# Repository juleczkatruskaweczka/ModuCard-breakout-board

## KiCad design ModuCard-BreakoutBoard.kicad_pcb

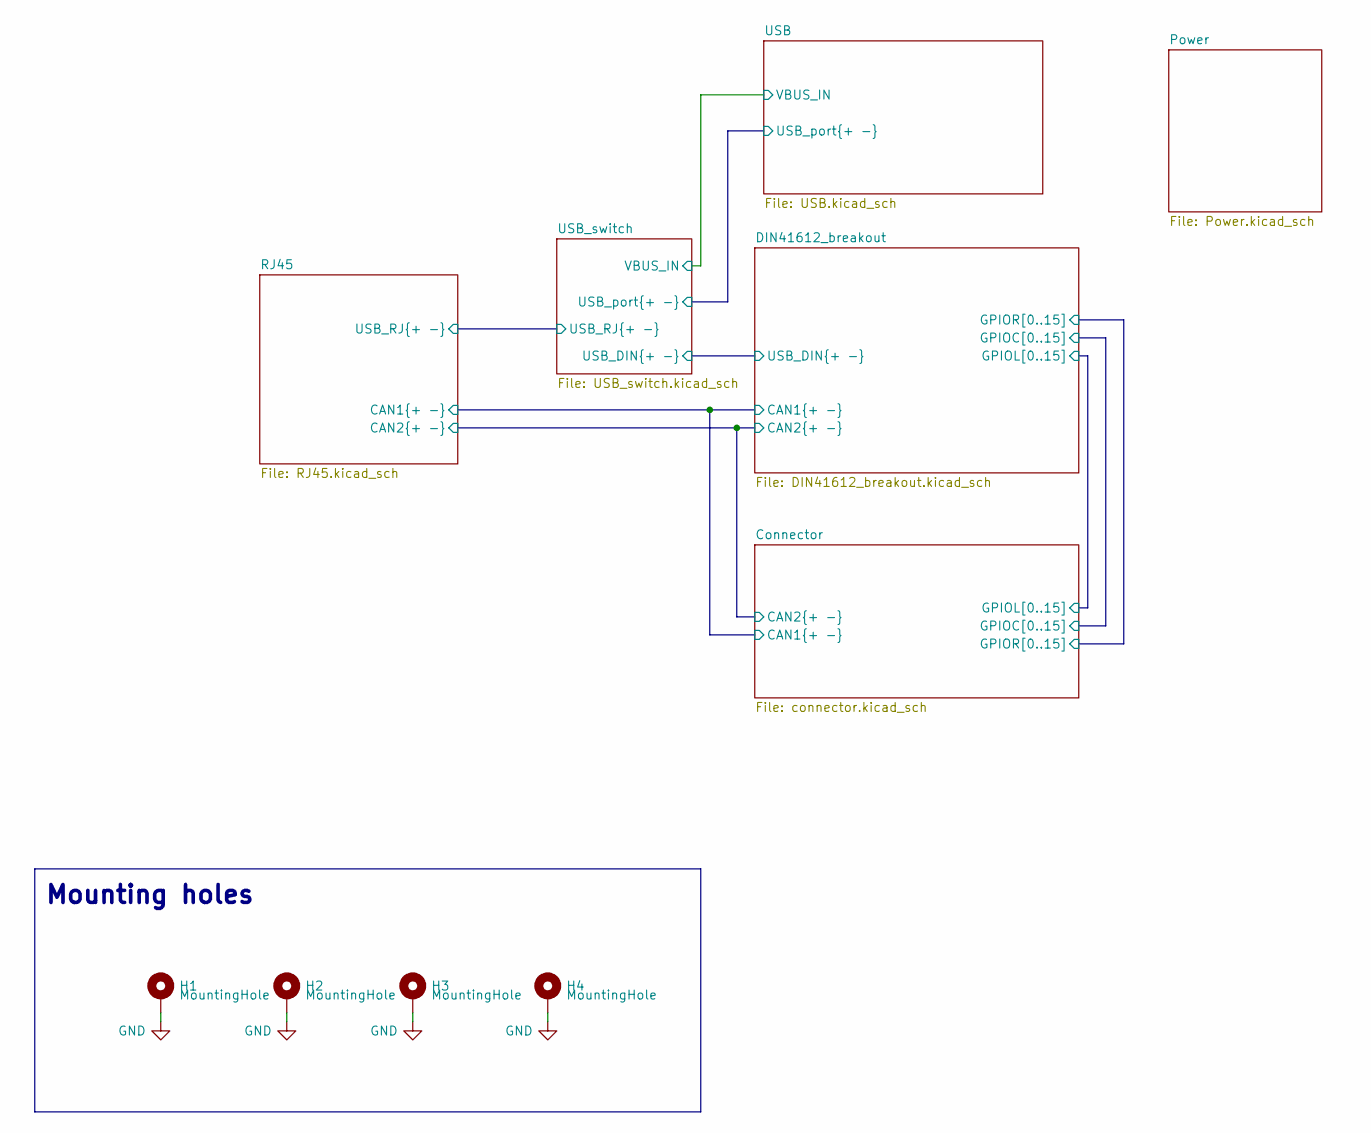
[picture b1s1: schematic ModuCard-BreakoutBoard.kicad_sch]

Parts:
H1, H2, H3, H4: MountingHole; MountingHole_2.7mm_M2.5_DIN965_Pad

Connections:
GND: H1.1, H2.1, H3.1, H4.1; also elsewhere on the board

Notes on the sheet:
Mounting holes

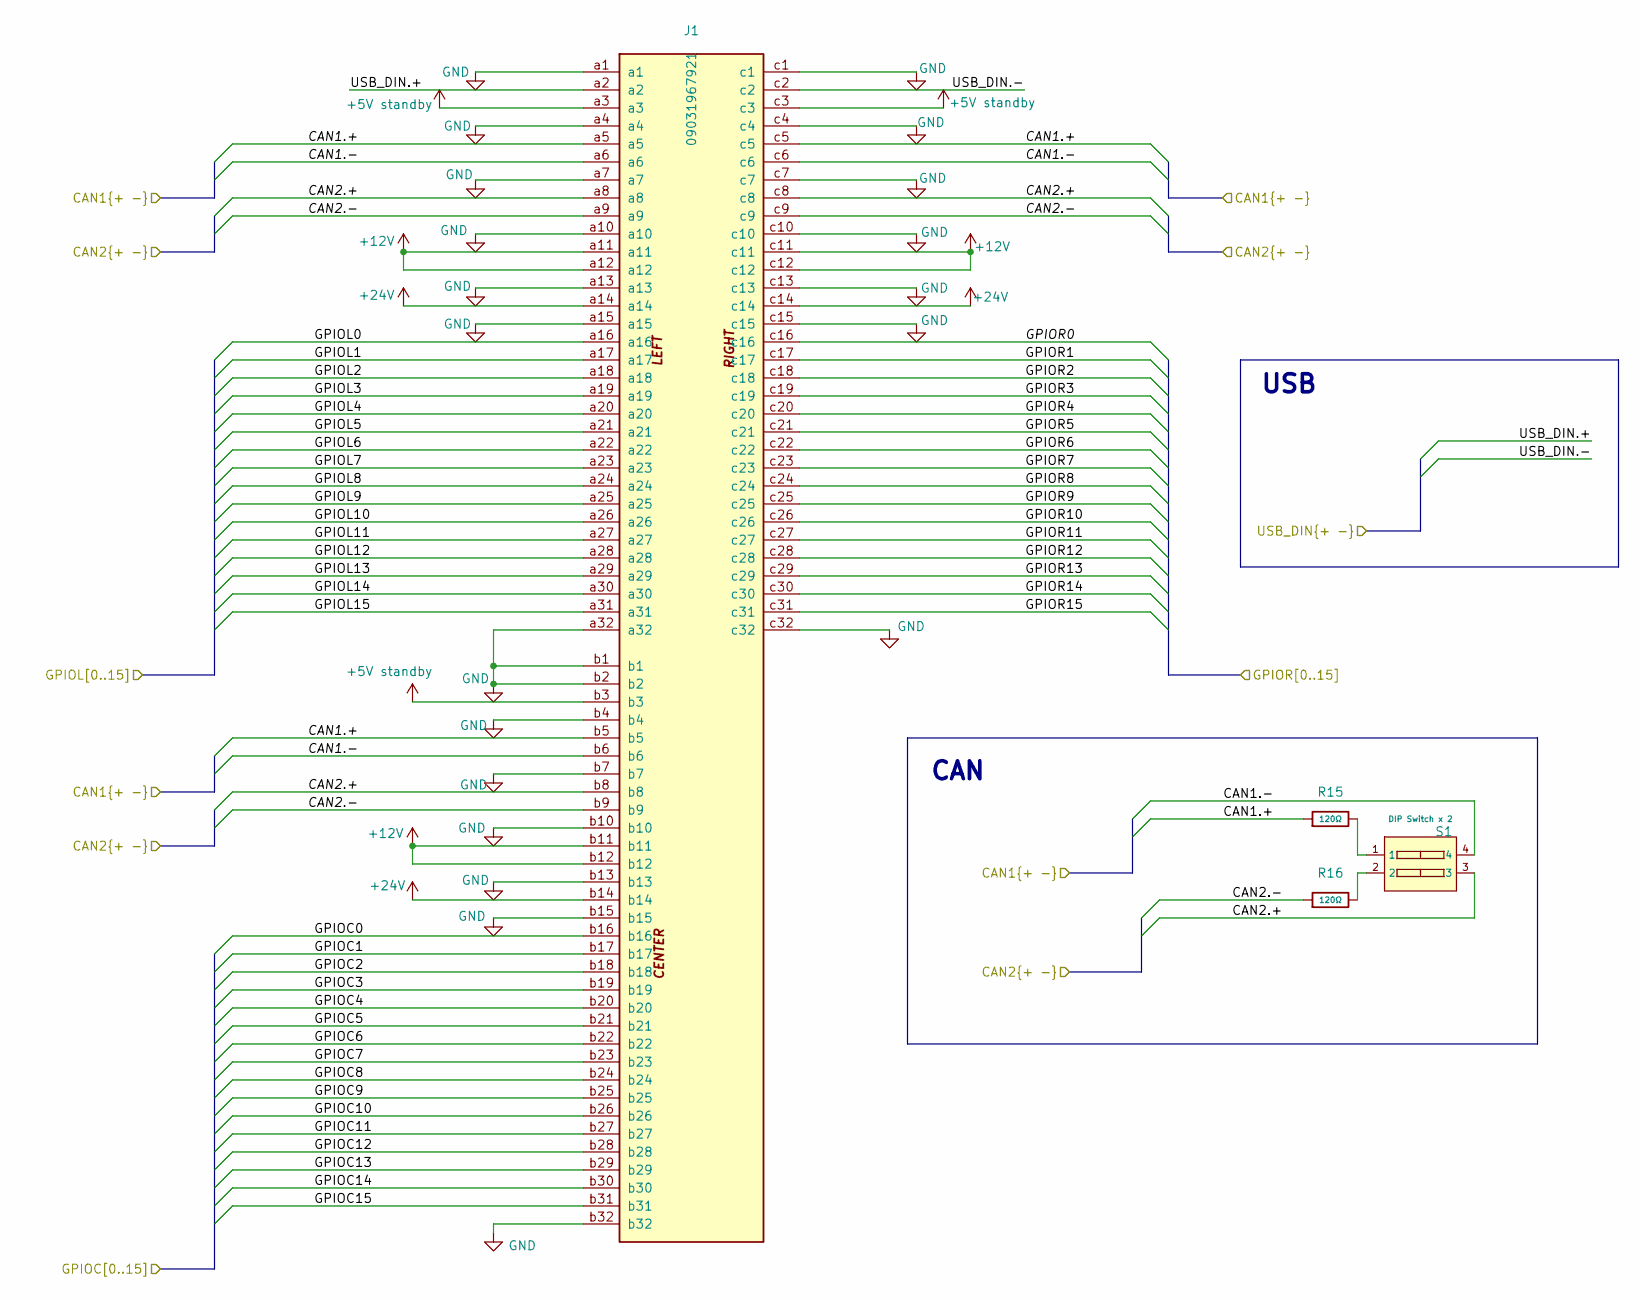
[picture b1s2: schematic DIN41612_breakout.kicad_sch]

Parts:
J1: 09031967921; DIN41612_R_3x32_Male_Vertical_THT; PARTREV D
R15, R16: 120Ω; R_0603; Overload Voltage (Max) 75V; Tolerance ±1%; Part 0603WAF1200T5E; LCSC C22787
S1: DIP Switch x 2; SW_DIP_SPSTx02_Slide_9.78x7.26mm_W7.62mm_P2.54mm; Current Rating 25mA; Voltage Rating 24V; Part 218-2LPSTR; LCSC C2961921

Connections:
+5V standby: J1.a3, J1.b3, J1.c3; also elsewhere on the board
+12V: J1.a11, J1.a12, J1.b11, J1.b12, J1.c11, J1.c12; also elsewhere on the board
+24V: J1.a14, J1.b14, J1.c14; also elsewhere on the board
/Connector/CAN1.+: J1.a5, J1.b5, J1.c5, R15.1; also elsewhere on the board
/Connector/CAN1.-: J1.a6, J1.b6, J1.c6, S1.4; also elsewhere on the board
/Connector/CAN2.+: J1.a8, J1.b8, J1.c8, S1.3; also elsewhere on the board
/Connector/CAN2.-: J1.a9, J1.b9, J1.c9, R16.1; also elsewhere on the board
/Connector/GPIOC0: J1.b16; also elsewhere on the board
/Connector/GPIOC1: J1.b17; also elsewhere on the board
/Connector/GPIOC2: J1.b18; also elsewhere on the board
/Connector/GPIOC3: J1.b19; also elsewhere on the board
/Connector/GPIOC4: J1.b20; also elsewhere on the board
/Connector/GPIOC5: J1.b21; also elsewhere on the board
/Connector/GPIOC6: J1.b22; also elsewhere on the board
/Connector/GPIOC7: J1.b23; also elsewhere on the board
/Connector/GPIOC8: J1.b24; also elsewhere on the board
/Connector/GPIOC9: J1.b25; also elsewhere on the board
/Connector/GPIOC10: J1.b26; also elsewhere on the board
/Connector/GPIOC11: J1.b27; also elsewhere on the board
/Connector/GPIOC12: J1.b28; also elsewhere on the board
/Connector/GPIOC13: J1.b29; also elsewhere on the board
/Connector/GPIOC14: J1.b30; also elsewhere on the board
/Connector/GPIOC15: J1.b31; also elsewhere on the board
/Connector/GPIOL0: J1.a16; also elsewhere on the board
/Connector/GPIOL1: J1.a17; also elsewhere on the board
/Connector/GPIOL2: J1.a18; also elsewhere on the board
/Connector/GPIOL3: J1.a19; also elsewhere on the board
/Connector/GPIOL4: J1.a20; also elsewhere on the board
/Connector/GPIOL5: J1.a21; also elsewhere on the board
/Connector/GPIOL6: J1.a22; also elsewhere on the board
/Connector/GPIOL7: J1.a23; also elsewhere on the board
/Connector/GPIOL8: J1.a24; also elsewhere on the board
/Connector/GPIOL9: J1.a25; also elsewhere on the board
/Connector/GPIOL10: J1.a26; also elsewhere on the board
/Connector/GPIOL11: J1.a27; also elsewhere on the board
/Connector/GPIOL12: J1.a28; also elsewhere on the board
/Connector/GPIOL13: J1.a29; also elsewhere on the board
/Connector/GPIOL14: J1.a30; also elsewhere on the board
/Connector/GPIOL15: J1.a31; also elsewhere on the board
/Connector/GPIOR0: J1.c16; also elsewhere on the board
/Connector/GPIOR1: J1.c17; also elsewhere on the board
/Connector/GPIOR2: J1.c18; also elsewhere on the board
/Connector/GPIOR3: J1.c19; also elsewhere on the board
/Connector/GPIOR4: J1.c20; also elsewhere on the board
/Connector/GPIOR5: J1.c21; also elsewhere on the board
/Connector/GPIOR6: J1.c22; also elsewhere on the board
/Connector/GPIOR7: J1.c23; also elsewhere on the board
/Connector/GPIOR8: J1.c24; also elsewhere on the board
/Connector/GPIOR9: J1.c25; also elsewhere on the board
/Connector/GPIOR10: J1.c26; also elsewhere on the board
/Connector/GPIOR11: J1.c27; also elsewhere on the board
/Connector/GPIOR12: J1.c28; also elsewhere on the board
/Connector/GPIOR13: J1.c29; also elsewhere on the board
/Connector/GPIOR14: J1.c30; also elsewhere on the board
/Connector/GPIOR15: J1.c31; also elsewhere on the board
/DIN41612_breakout/USB_DIN.+: J1.a2; also elsewhere on the board
/DIN41612_breakout/USB_DIN.-: J1.c2; also elsewhere on the board
GND: J1.a1, J1.a4, J1.a7, J1.a10, J1.a13, J1.a15, J1.a32, J1.b1, J1.b2, J1.b4, J1.b7, J1.b10, J1.b13, J1.b15, J1.b32, J1.c1, J1.c4, J1.c7, J1.c10, J1.c13, J1.c15, J1.c32; also elsewhere on the board
unnamed: R15.2, S1.1
unnamed: R16.2, S1.2

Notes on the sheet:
CAN
USB

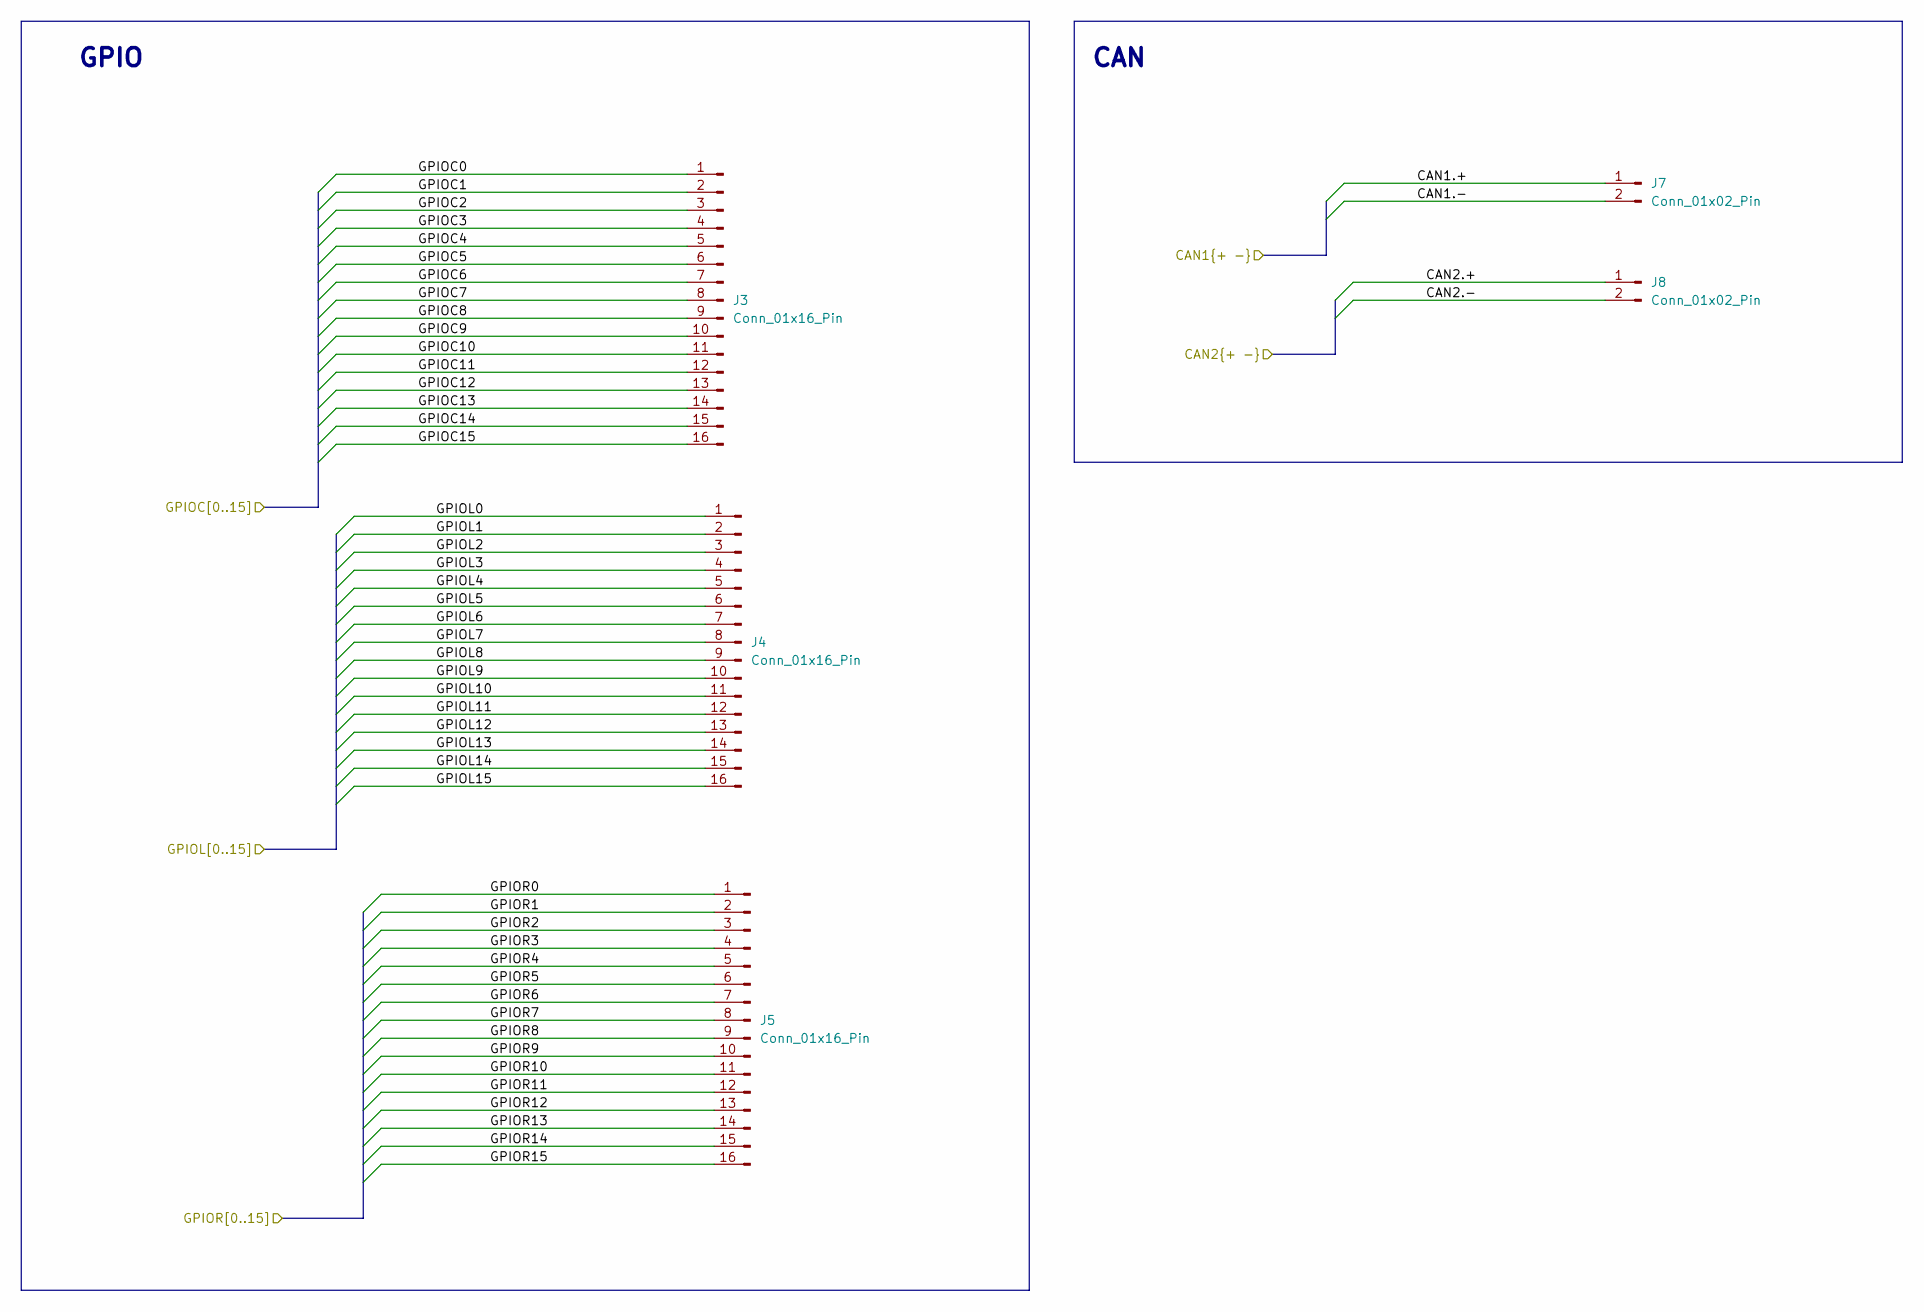
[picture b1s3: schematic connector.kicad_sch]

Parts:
J3, J4, J5: Conn_01x16_Pin; PinHeader_1x16_P2.54mm_Vertical
J7, J8: Conn_01x02_Pin; PinHeader_1x02_P2.54mm_Vertical

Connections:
/Connector/CAN1.+: J7.1; also elsewhere on the board
/Connector/CAN1.-: J7.2; also elsewhere on the board
/Connector/CAN2.+: J8.1; also elsewhere on the board
/Connector/CAN2.-: J8.2; also elsewhere on the board
/Connector/GPIOC0: J3.1; also elsewhere on the board
/Connector/GPIOC1: J3.2; also elsewhere on the board
/Connector/GPIOC2: J3.3; also elsewhere on the board
/Connector/GPIOC3: J3.4; also elsewhere on the board
/Connector/GPIOC4: J3.5; also elsewhere on the board
/Connector/GPIOC5: J3.6; also elsewhere on the board
/Connector/GPIOC6: J3.7; also elsewhere on the board
/Connector/GPIOC7: J3.8; also elsewhere on the board
/Connector/GPIOC8: J3.9; also elsewhere on the board
/Connector/GPIOC9: J3.10; also elsewhere on the board
/Connector/GPIOC10: J3.11; also elsewhere on the board
/Connector/GPIOC11: J3.12; also elsewhere on the board
/Connector/GPIOC12: J3.13; also elsewhere on the board
/Connector/GPIOC13: J3.14; also elsewhere on the board
/Connector/GPIOC14: J3.15; also elsewhere on the board
/Connector/GPIOC15: J3.16; also elsewhere on the board
/Connector/GPIOL0: J4.1; also elsewhere on the board
/Connector/GPIOL1: J4.2; also elsewhere on the board
/Connector/GPIOL2: J4.3; also elsewhere on the board
/Connector/GPIOL3: J4.4; also elsewhere on the board
/Connector/GPIOL4: J4.5; also elsewhere on the board
/Connector/GPIOL5: J4.6; also elsewhere on the board
/Connector/GPIOL6: J4.7; also elsewhere on the board
/Connector/GPIOL7: J4.8; also elsewhere on the board
/Connector/GPIOL8: J4.9; also elsewhere on the board
/Connector/GPIOL9: J4.10; also elsewhere on the board
/Connector/GPIOL10: J4.11; also elsewhere on the board
/Connector/GPIOL11: J4.12; also elsewhere on the board
/Connector/GPIOL12: J4.13; also elsewhere on the board
/Connector/GPIOL13: J4.14; also elsewhere on the board
/Connector/GPIOL14: J4.15; also elsewhere on the board
/Connector/GPIOL15: J4.16; also elsewhere on the board
/Connector/GPIOR0: J5.1; also elsewhere on the board
/Connector/GPIOR1: J5.2; also elsewhere on the board
/Connector/GPIOR2: J5.3; also elsewhere on the board
/Connector/GPIOR3: J5.4; also elsewhere on the board
/Connector/GPIOR4: J5.5; also elsewhere on the board
/Connector/GPIOR5: J5.6; also elsewhere on the board
/Connector/GPIOR6: J5.7; also elsewhere on the board
/Connector/GPIOR7: J5.8; also elsewhere on the board
/Connector/GPIOR8: J5.9; also elsewhere on the board
/Connector/GPIOR9: J5.10; also elsewhere on the board
/Connector/GPIOR10: J5.11; also elsewhere on the board
/Connector/GPIOR11: J5.12; also elsewhere on the board
/Connector/GPIOR12: J5.13; also elsewhere on the board
/Connector/GPIOR13: J5.14; also elsewhere on the board
/Connector/GPIOR14: J5.15; also elsewhere on the board
/Connector/GPIOR15: J5.16; also elsewhere on the board

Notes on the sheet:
CAN
GPIO

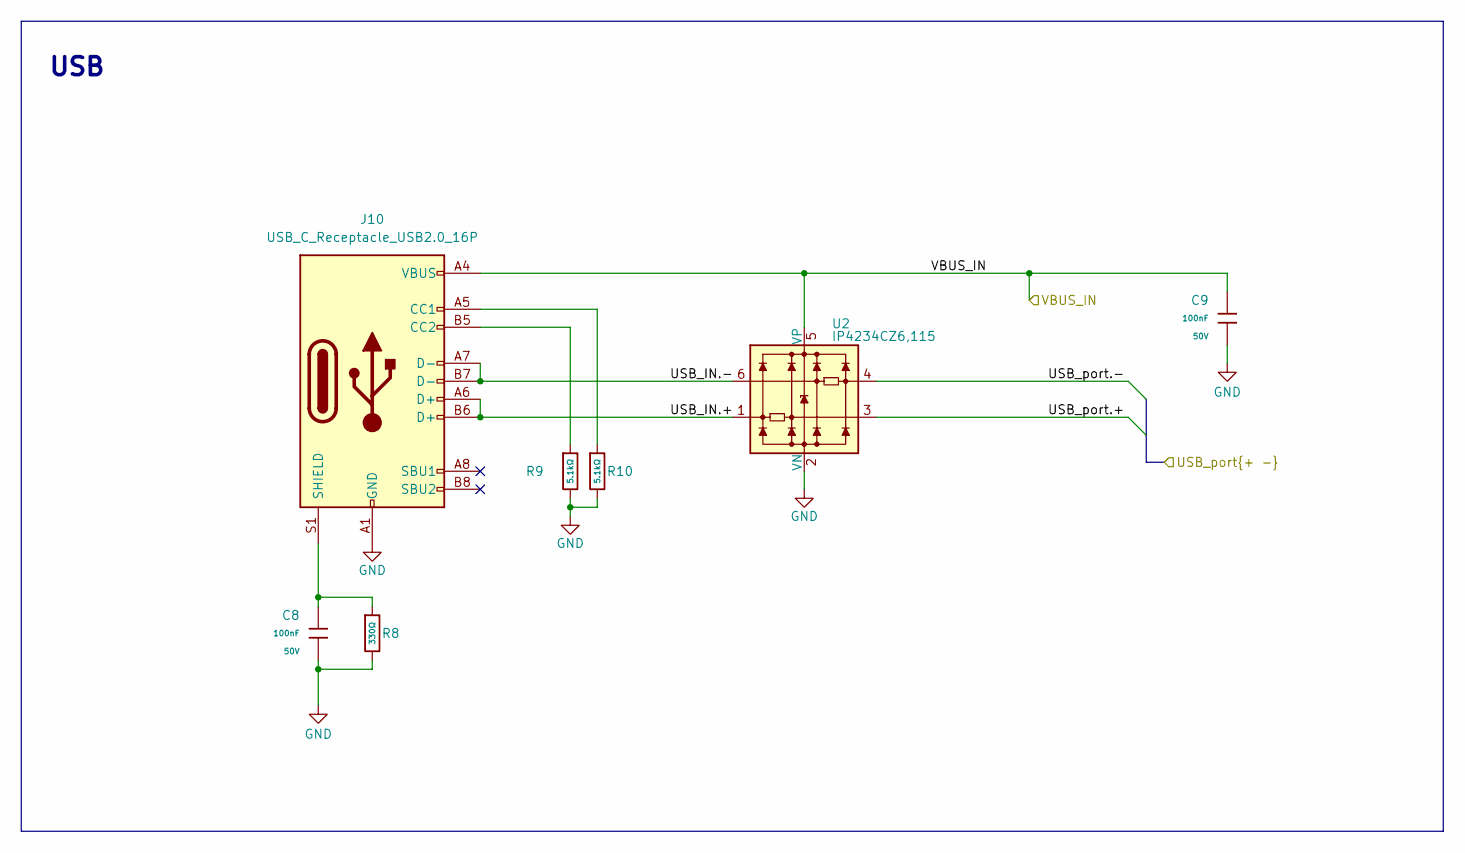
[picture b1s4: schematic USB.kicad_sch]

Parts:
C8, C9: 100nF; C_0402; Voltage Rated 50V; Tolerance ±10%; Part CL05B104KB54PNC; LCSC C307331
J10: USB_C_Receptacle_USB2.0_16P; USB_C_Receptacle_GCT_USB4105-xx-A_16P_TopMnt_Horizontal
R8: 330Ω; R_0402; Overload Voltage (Max) 50V; Tolerance ±1%; Part 0402WGF3300TCE; LCSC C25104
R9, R10: 5.1kΩ; R_0402; Overload Voltage (Max) 50V; Tolerance ±1%; Part 0402WGF5101TCE; LCSC C25905
U2: IP4234CZ6,115; SC-74-6_1.55x2.9mm_P0.95mm

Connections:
/USB/USB_IN.+: J10.A6 (D+), J10.B6 (D+), U2.1
/USB/USB_IN.-: J10.A7 (D-), J10.B7 (D-), U2.6
/USB/USB_port.+: U2.3; also elsewhere on the board
/USB/USB_port.-: U2.4; also elsewhere on the board
/USB/VBUS_IN: C9.1, J10.A4 (VBUS), J10.A9 (VBUS), J10.B4 (VBUS), J10.B9 (VBUS), U2.5 (VP); also elsewhere on the board
GND: C8.2, C9.2, J10.A1 (GND), J10.A12 (GND), J10.B1 (GND), J10.B12 (GND), R8.2, R9.2, R10.2, U2.2 (VN); also elsewhere on the board
unnamed: J10.A5 (CC1), R10.1
unnamed: J10.B5 (CC2), R9.1
unnamed: C8.1, J10.S1 (SHIELD), R8.1

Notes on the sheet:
USB

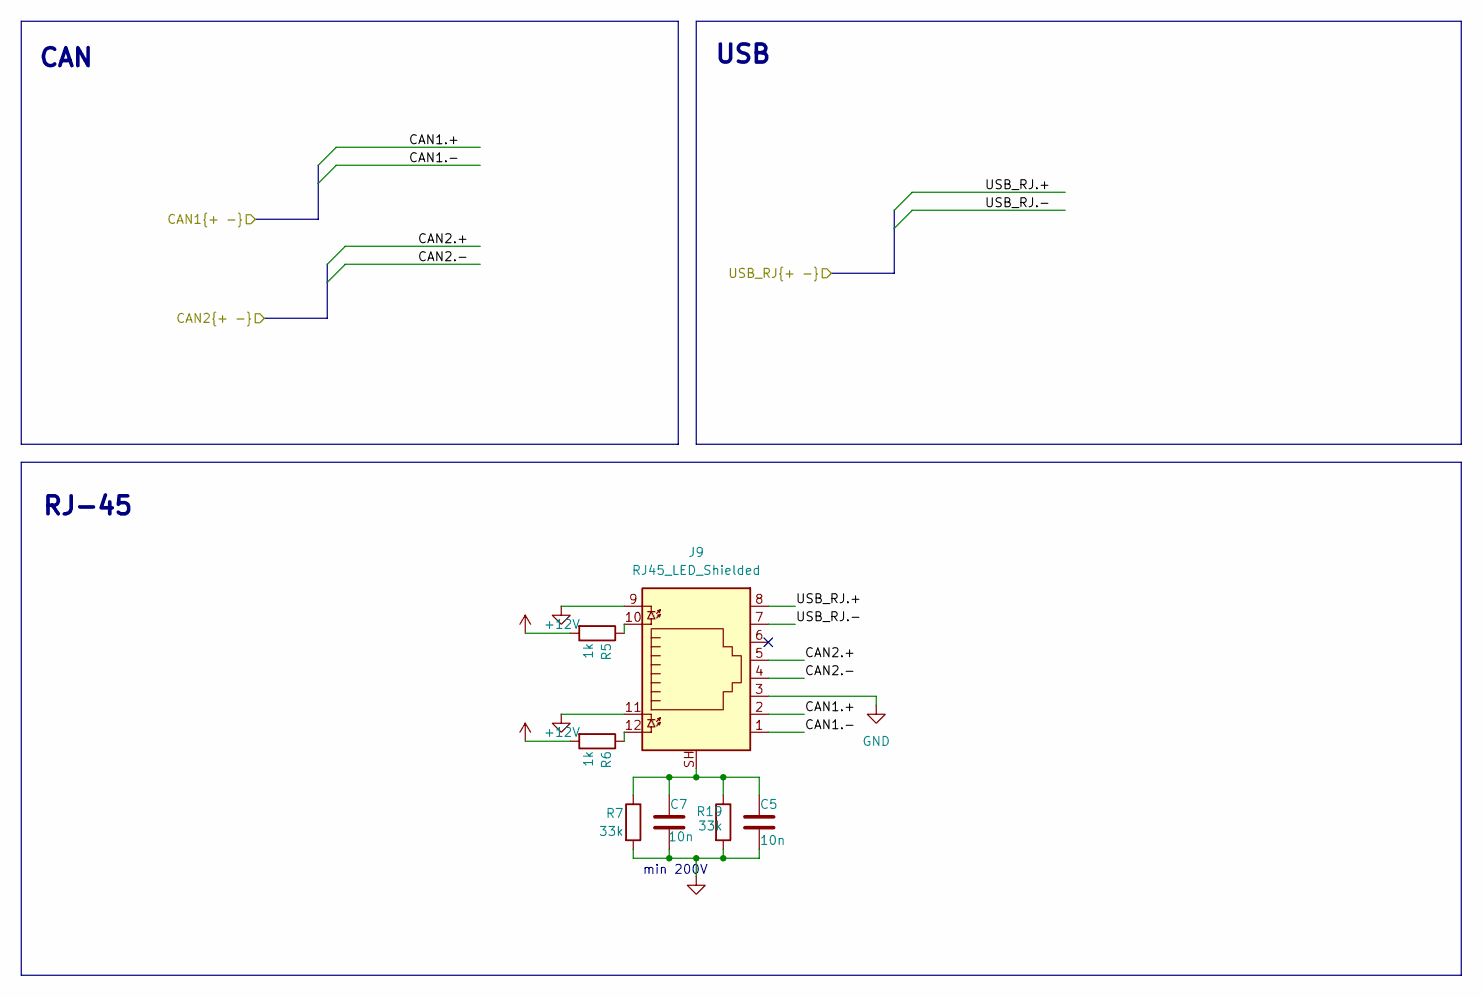
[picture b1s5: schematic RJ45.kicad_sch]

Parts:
C5, C7: 10n; C_0402_1005Metric
J9: RJ45_LED_Shielded; RJ45_Amphenol_RJHSE538X
R5, R6: 1k; R_0402_1005Metric
R7, R19: 33k; R_0402_1005Metric

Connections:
+12V: R5.2, R6.2; also elsewhere on the board
/Connector/CAN1.+: J9.2; also elsewhere on the board
/Connector/CAN1.-: J9.1; also elsewhere on the board
/Connector/CAN2.+: J9.5; also elsewhere on the board
/Connector/CAN2.-: J9.4; also elsewhere on the board
/RJ45/USB_RJ.+: J9.8; also elsewhere on the board
/RJ45/USB_RJ.-: J9.7; also elsewhere on the board
GND: C5.2, C7.2, J9.3, J9.9, J9.11, R7.2, R19.2; also elsewhere on the board
unnamed: C5.1, C7.1, J9.SH, R7.1, R19.1
unnamed: J9.10, R5.1
unnamed: J9.12, R6.1

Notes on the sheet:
USB
RJ-45
min 200V
CAN

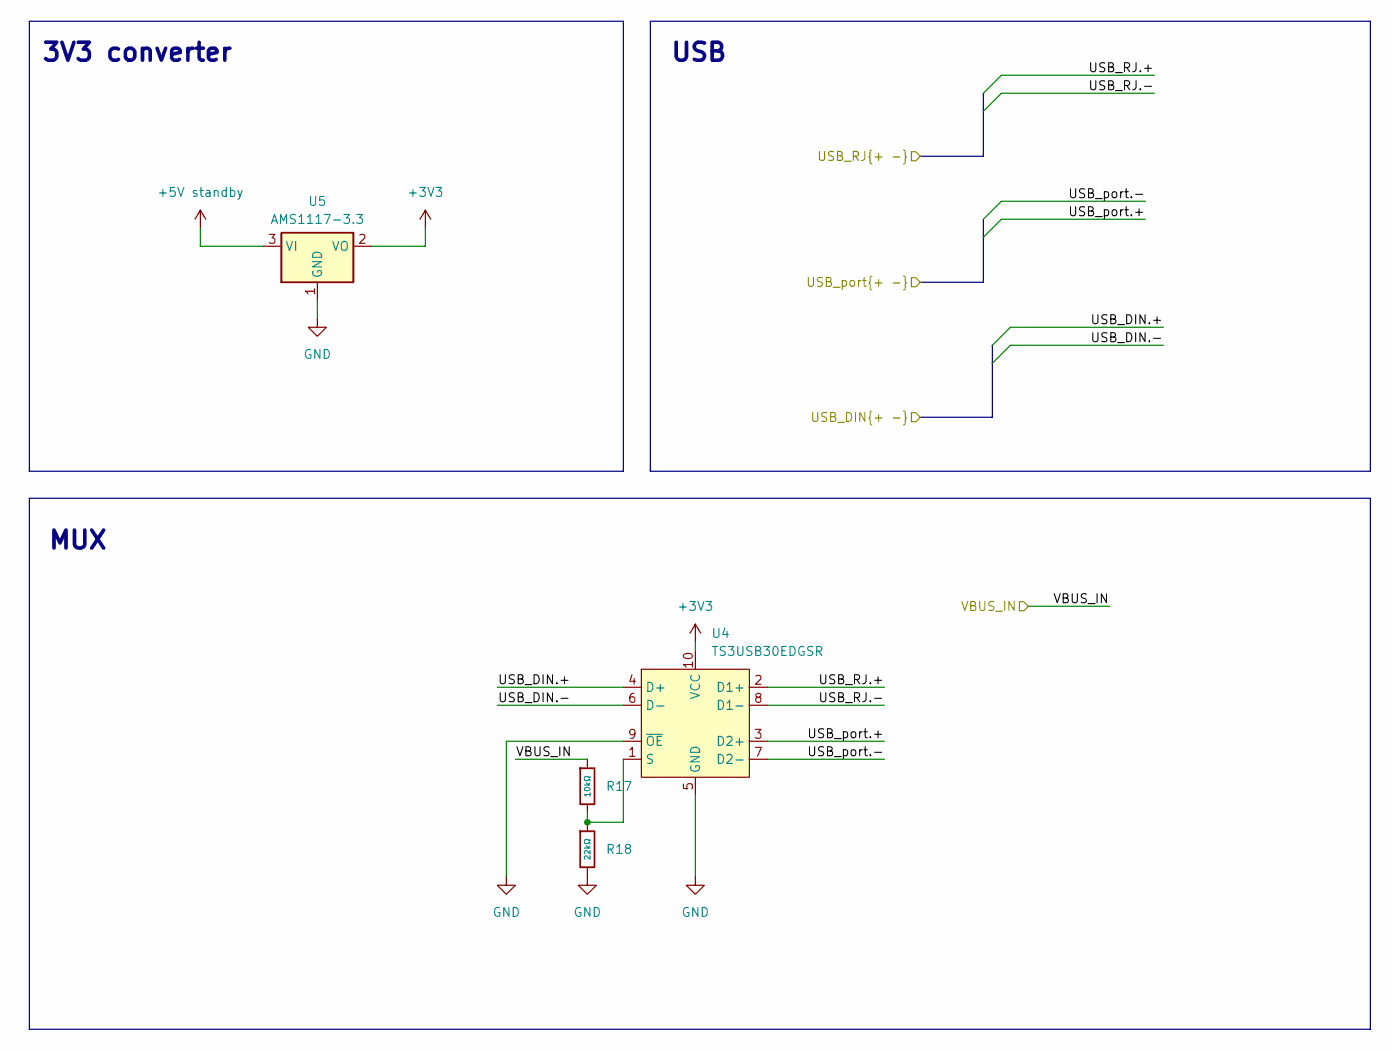
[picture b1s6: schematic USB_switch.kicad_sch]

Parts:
R17: 10kΩ; R_0603; Overload Voltage (Max) 75V; Tolerance ±1%; Part 0603WAF1002T5E; LCSC C25804
R18: 22kΩ; R_0402; Overload Voltage (Max) 50V; Tolerance ±1%; Part 0402WGF2202TCE; LCSC C25768
U4: TS3USB30EDGSR; VSSOP-10_3x3mm_P0.5mm
U5: AMS1117-3.3; SOT-223-3_TabPin2

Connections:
+3V3: U4.10 (VCC), U5.2 (VO)
+5V standby: U5.3 (VI); also elsewhere on the board
/DIN41612_breakout/USB_DIN.+: U4.4 (D+); also elsewhere on the board
/DIN41612_breakout/USB_DIN.-: U4.6 (D-); also elsewhere on the board
/RJ45/USB_RJ.+: U4.2 (D1+); also elsewhere on the board
/RJ45/USB_RJ.-: U4.8 (D1-); also elsewhere on the board
/USB/USB_port.+: U4.3 (D2+); also elsewhere on the board
/USB/USB_port.-: U4.7 (D2-); also elsewhere on the board
/USB/VBUS_IN: R17.1; also elsewhere on the board
GND: R18.2, U4.5 (GND), U4.9 (~OE), U5.1 (GND); also elsewhere on the board
unnamed: R17.2, R18.1, U4.1 (S)

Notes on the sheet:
USB
MUX
3V3 converter

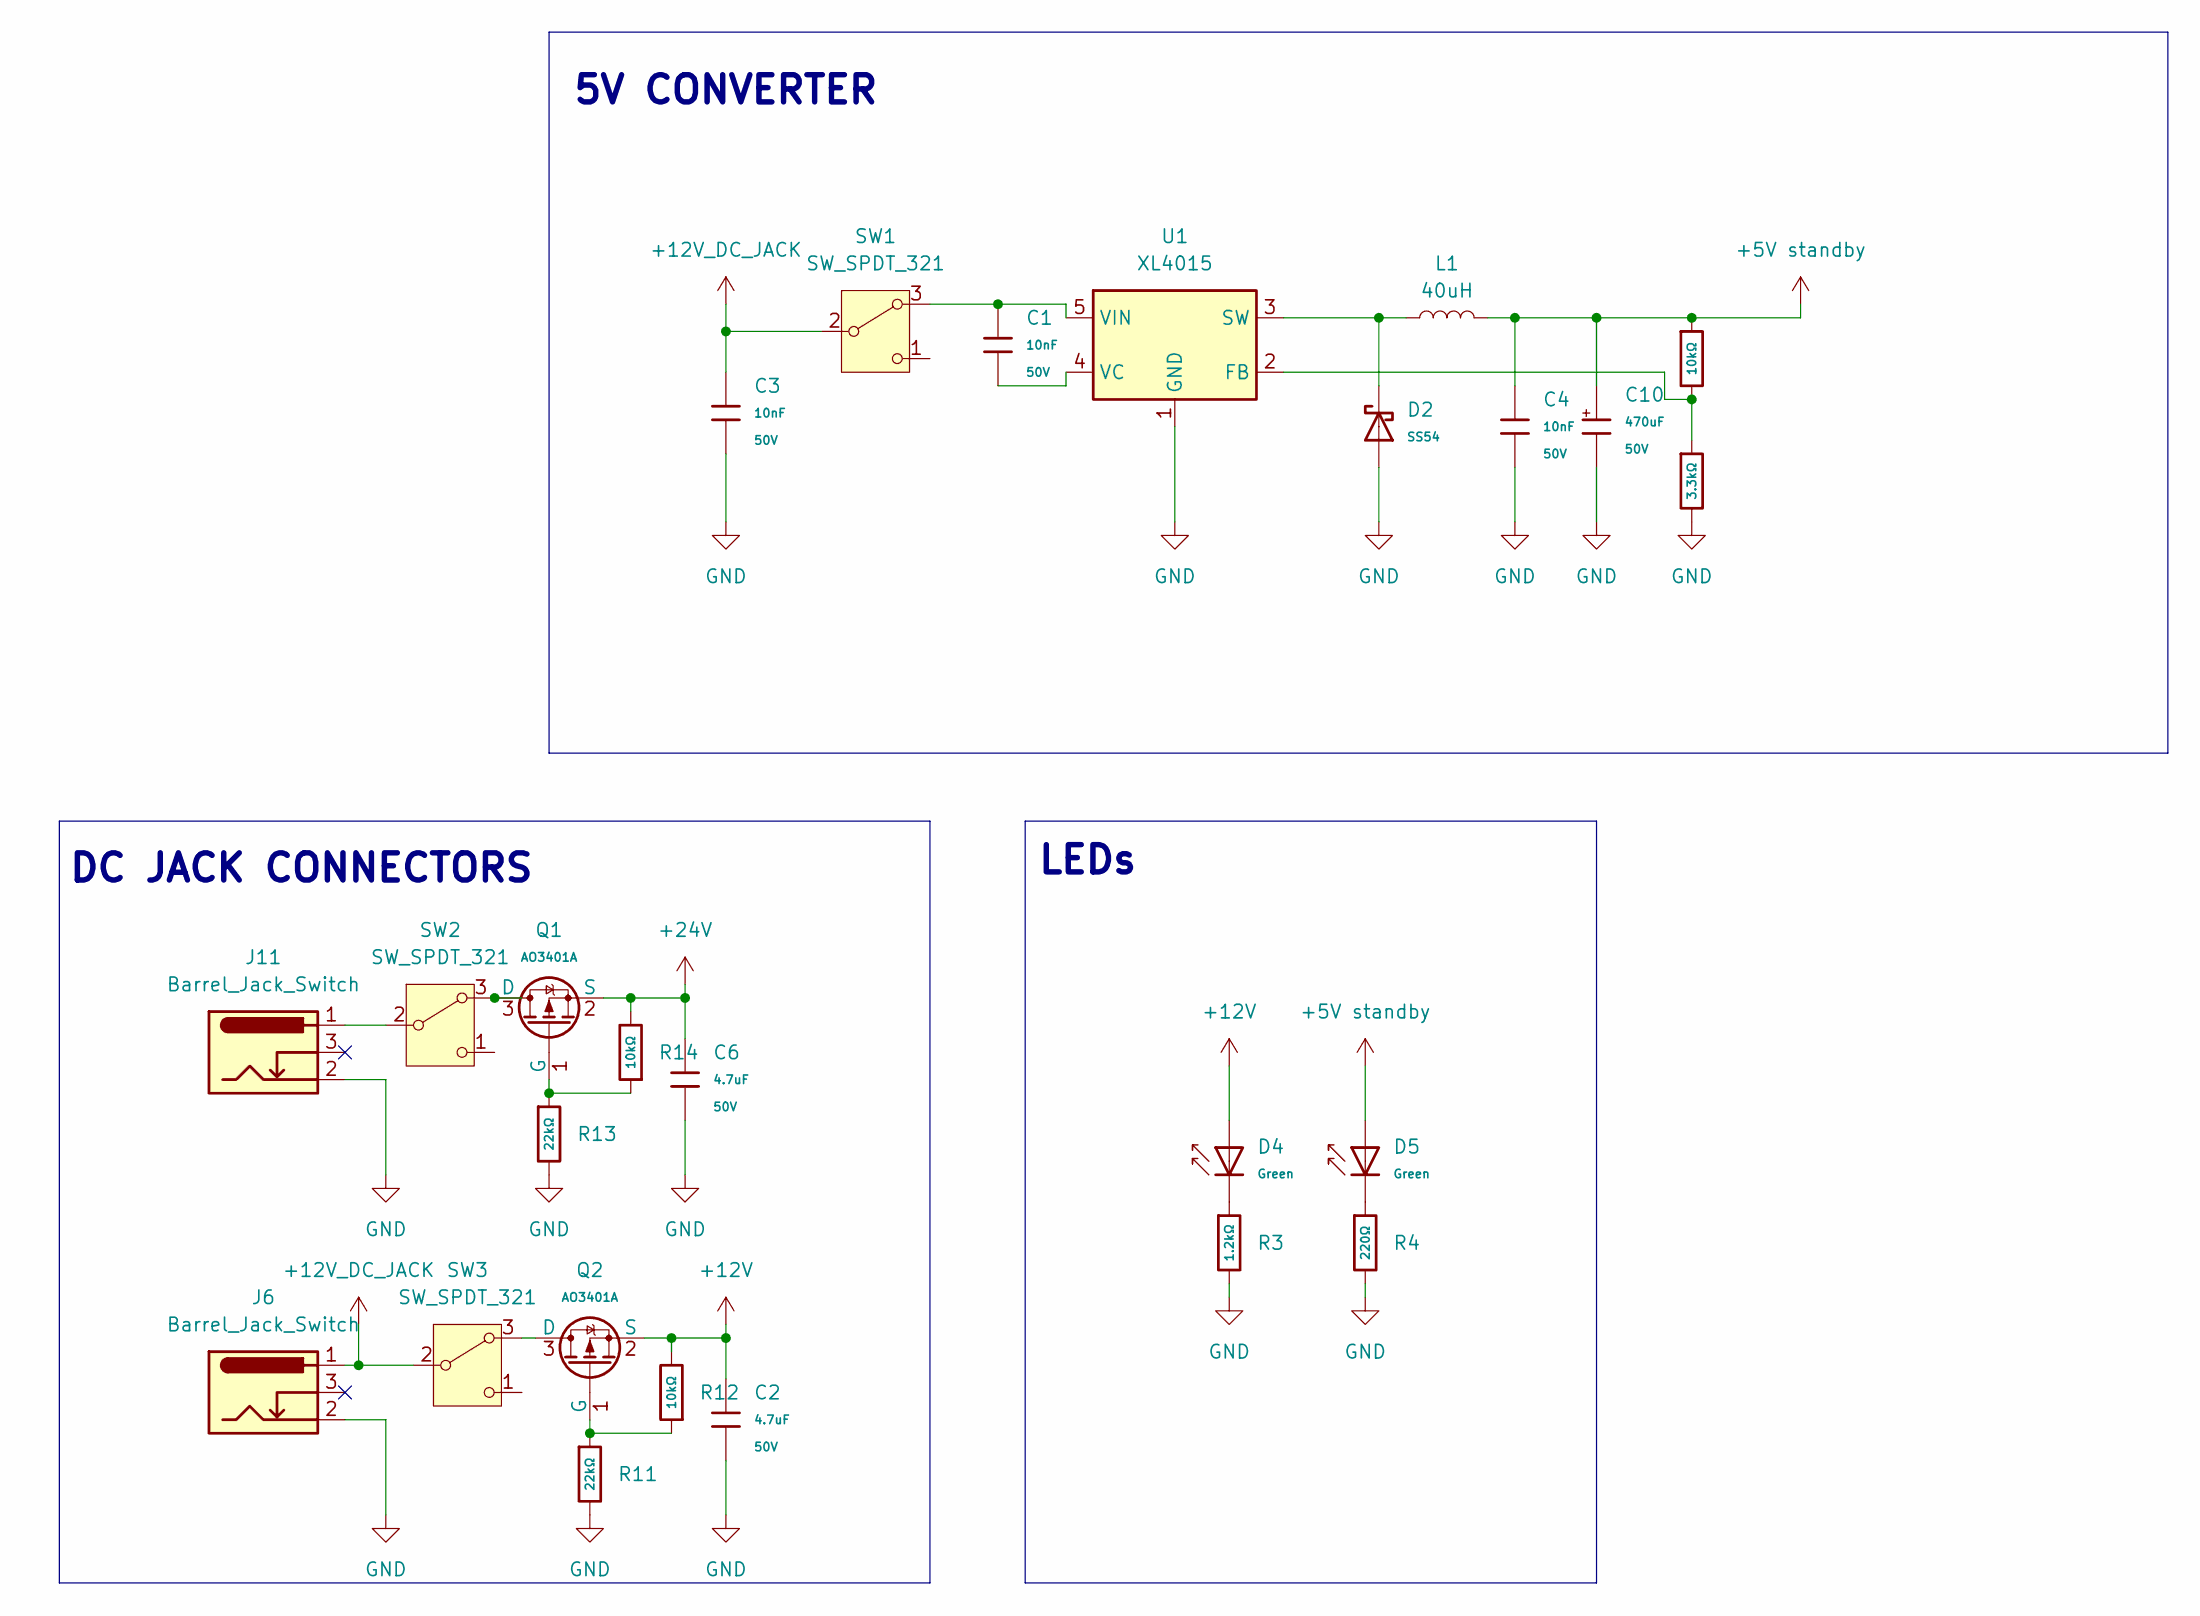
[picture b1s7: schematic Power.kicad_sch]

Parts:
C1, C3, C4: 10nF; C_0402; Voltage Rated 50V; Tolerance ±10%; Part CL05B103KB5NNNC; LCSC C15195
C2, C6: 4.7uF; C_1206; Voltage Rated 50V; Tolerance ±10%; Part 1206B475K500NT; LCSC C29823
C10: 470uF; C_Plugin,D10xL16mm; Voltage Rated 50V; Part EGT477M1HG16RRS0P; LCSC C3015599
D2: SS54; D_SMA; Forward Voltage (Vf@If) 550mV@5A; Reverse Voltage (Vr) 40V; Part SS54; LCSC C22452
D4, D5: Green; D_0603; Part 19-217/GHC-YR1S2/6T; LCSC C2986059
J6, J11: Barrel_Jack_Switch; BarrelJack_Kycon_KLDX-0202-xC_Horizontal
L1: 40uH; L_Bourns_SRR1260
Q1, Q2: AO3401A; Q_SOT-23; Part AO3401A; LCSC C15127
R1, R12, R14: 10kΩ; R_0603; Overload Voltage (Max) 75V; Tolerance ±1%; Part 0603WAF1002T5E; LCSC C25804
R2: 3.3kΩ; R_0402; Overload Voltage (Max) 50V; Tolerance ±1%; Part 0402WGF3301TCE; LCSC C25890
R3: 1.2kΩ; R_0402; Overload Voltage (Max) 50V; Tolerance ±1%; Part 0402WGF1201TCE; LCSC C25862
R4: 220Ω; R_0402; Overload Voltage (Max) 50V; Tolerance ±1%; Part 0402WGF2200TCE; LCSC C25091
R11, R13: 22kΩ; R_0402; Overload Voltage (Max) 50V; Tolerance ±1%; Part 0402WGF2202TCE; LCSC C25768
SW1, SW2, SW3: SW_SPDT_321; SW_Toggle_Blue_wSlots
U1: XL4015; TO-263-5_TabPin3

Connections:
+5V standby: C4.1, C10.1, D5.2, L1.2, R1.1; also elsewhere on the board
+12V: C2.1, D4.2, Q2.2 (S), R12.2; also elsewhere on the board
+12V_DC_JACK: C3.1, J6.1, SW1.2 (B), SW3.2 (B)
+24V: C6.1, Q1.2 (S), R14.2; also elsewhere on the board
GND: C2.2, C3.2, C4.2, C6.2, C10.2, D2.2, J6.2, J11.2, R2.2, R3.2, R4.2, R11.2, R13.2, U1.1 (GND); also elsewhere on the board
unnamed: D4.1, R3.1
unnamed: D5.1, R4.1
unnamed: Q1.3 (D), SW2.3 (A)
unnamed: Q1.1 (G), R13.1, R14.1
unnamed: Q2.3 (D), SW3.3 (A)
unnamed: Q2.1 (G), R11.1, R12.1
unnamed: C1.1, SW1.3 (A), U1.5 (VIN)
unnamed: J11.1, SW2.2 (B)
unnamed: R1.2, R2.1, U1.2 (FB)
unnamed: D2.1, L1.1, U1.3 (SW)
unnamed: C1.2, U1.4 (VC)

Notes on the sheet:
LEDs
5V CONVERTER
DC JACK CONNECTORS

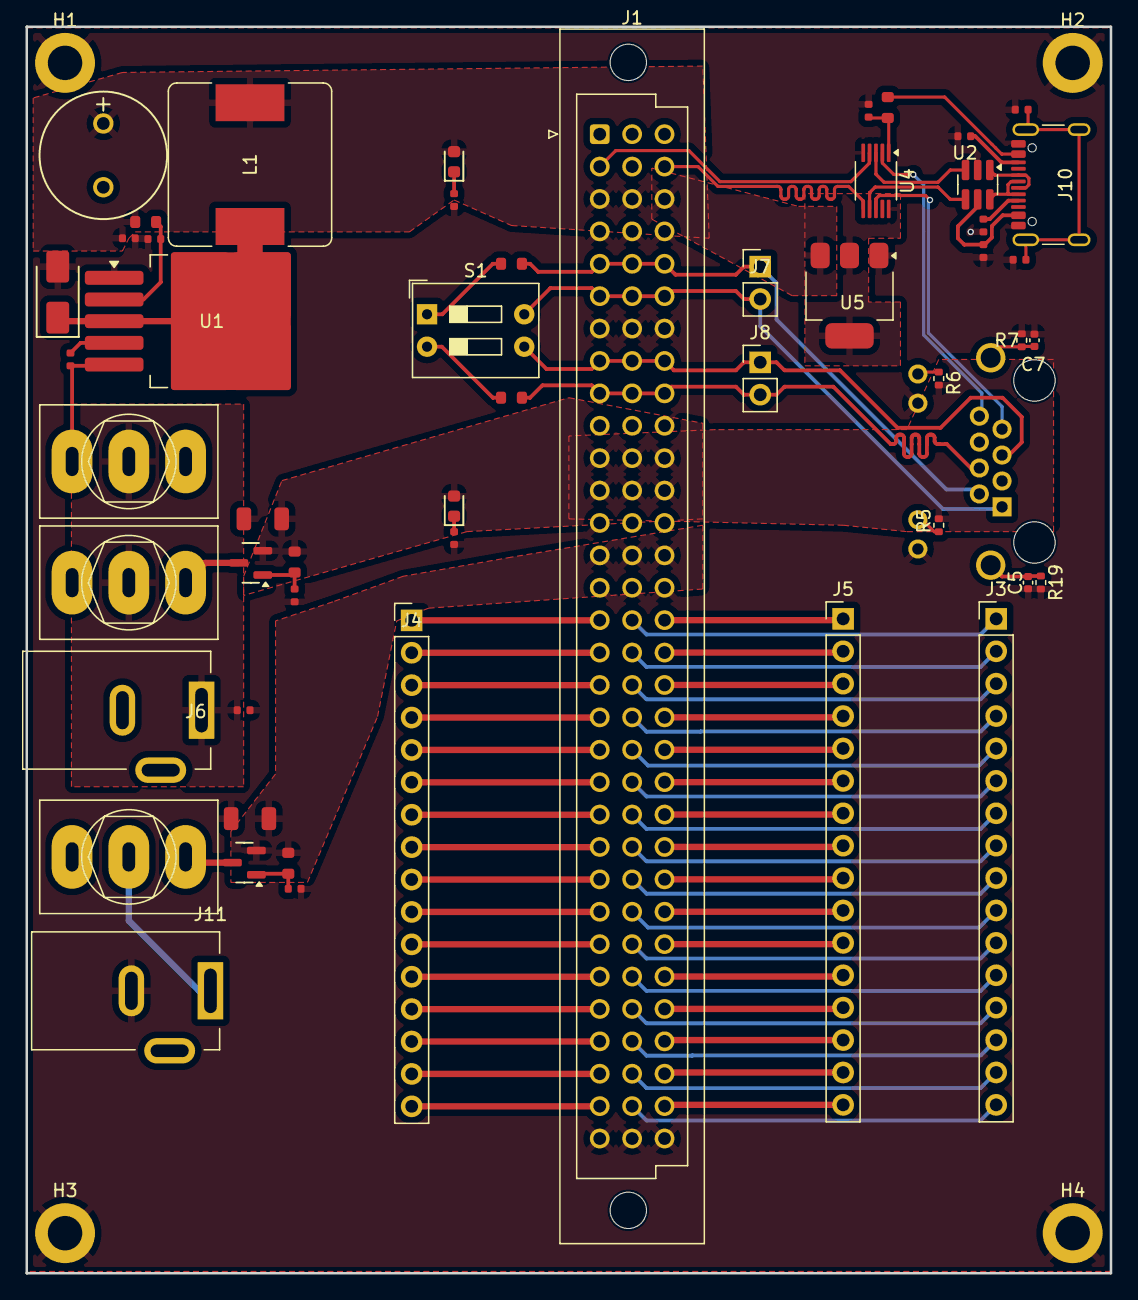
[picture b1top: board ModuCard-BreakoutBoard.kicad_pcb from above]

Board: 4 copper layers, 85.0 x 97.7 mm, 57 parts (1 on the bottom side), 87 nets.

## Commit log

2025-02-15 Create schematic
2025-02-15 Add DC Jack footprint
2025-02-15 Add connectors footprints
2025-02-16 Change power source
2025-02-16 Create fundamental layout
2025-02-16 Change inductor model
2025-02-16 Fix converter placement
2025-02-17 Change PCB size
2025-02-19 Add DIP switches
2025-02-19 Fix typo
2025-02-19 Change USB net names
2025-02-19 Add multiplexer for USB
2025-02-19 Change voltage value
2025-02-19 Fix paths
2025-02-19 Fix USB connection
2025-02-19 Finish layout
2025-02-19 Change DRC rules
2025-02-19 Make paths
2025-02-19 Add mounting holes
2025-02-26 Change capacitor
2025-02-26 Change DIP switch footprint
2025-02-26 Update page numbers
2025-02-26 Add USB and CAN path settings
2025-02-26 Change layout
2025-02-26 Add path settings
2025-02-26 Change DIP switch connection
2025-02-26 Improve layout, add paths
2025-03-14 Add extra capacitor and resistor
2025-03-14 Change schematic
2025-03-14 Fix errors
